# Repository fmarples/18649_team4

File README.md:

# Team 4 Lab 2

**Managed session:** `start.py` starts/connects the Pi bridge and wheel GUI;
`stop.py` stops only the managed pair. Start can cause motion; keep hands clear
and pedals released. See [session ownership and logs](doc/ONE_CLICK_START.md).

`main` contains the combined Part 3 actuator implementation and Part 4 Zephyr
scheduling. Use the current firmware for combined motor, brake, steering and
blinker testing; there is no separate Part 4 application or required rollback.
Part 3.5 ADC acquisition is implemented with nominal ACS712 5A calibration and
upper-ADC-rail clipping at -4320 mA for reversed motor sensors and +4320 mA for
servo. There is no symmetric current cap. Physical calibration and combined timing remain pending.

## Code

- `stm32_zephyr/`: NUCLEO-F401RE firmware, UART parsing, motor/PID control,
  steering, blinkers, self-test, scheduling, current interface and timing markers.
- `pi/`: UDP-to-UART bridge, CRC protocol and optional GPIO timing markers.
- `windows/`: wheel-proxy launcher with event-filtered physical-input logs and
  read-only current charts, servo console and firmware build helper.
- `bringup/encoder_test/` and `bringup/motor_test/`: independent diagnostics.
- `tests/` and `test_protocol.py`: software and explicitly invoked hardware tests.
- `tools/`: generated-build checks, bounded QEMU runner and status-log summary.

The Part 3 integration commit is `3b04a43`; the Part 4 implementation commit is
`18da014`. The retired branches are preserved as archive tags.

## Architecture and operating policy

`Logitech wheel -> Windows proxy -> UDP 8000 -> Pi -> USART1 -> STM32 actuators`

The Pi link uses 115200 baud, 8N1. Commands carry raw wheel/pedal values and
buttons; status carries system state and current validity. Deploy matching
Pi and STM32 versions and all `pi/*.py` dependencies together. Read-only status
returns to the laptop on UDP 8002, separate from force-feedback UDP 8001.

One priority-1 owner applies motor outputs before steering and lamps. Status,
current sampling and USB diagnostics run at priorities 2, 3 and 4 respectively.
The three current channels use ADC1 with nominal calibration; failed or stale
acquisition is unavailable. Current telemetry does not control actuators.

Steering embeds the tracked 1200/1600/2000 us calibration. Boot and fault/link
recovery wait for healthy Pi commands and a centered wheel before LIVE. Vehicle
steering does not require a USB heartbeat; manual calibration retains its lease.
The servo console's OFF command does not stop motors. See the
[integration design](doc/INTEGRATION.md) and [protocol](PROTOCOL.md) for details.

## Team documentation

- [September 28 bench summary: changes, tests and remaining work](doc/SESSION_2026-09-28.md)
- [Actuator stability investigation and verification](doc/ACTUATOR_STABILITY.md)
- [Task table and scheduling rationale](PART4_TASK_TABLE.md)
- [Hardware BOM/power record](doc/HARDWARE.md) and [pin assignments](doc/LAB3_PINOUT.md)
- [Encoder calibration](doc/ENCODER_SPEC.md) and [motor characterization](doc/MOTOR_CHARACTERIZATION.md)
- [Current-sensor backend contract](doc/CURRENT_SENSOR_HANDOFF.md)
- [GUI telemetry and physical input logging](doc/GUI_TELEMETRY.md)
- [ADC hang diagnosis and grounding verification](doc/CURRENT_ADC_DIAGNOSIS.md)
- [Centered-start steering policy and evidence](doc/STEERING_AUTONOMOUS.md)
- [Timing points and measurement method](doc/PART4_TIMING.md)
- [Blank measurement worksheet](doc/PART4_MEASUREMENTS.csv)
- [Software verification record](doc/PART4_SOFTWARE_RESULTS.md)
- [Steering evidence](doc/PART3_3_RESULTS.md) and [blinker evidence](doc/PART3_4_RESULTS.md)
- [Lab 2 handout](doc/18-449_649%20Lab2%20-%20Sensors%20and%20Actuators%20v1_0.pdf)

The integrated image builds and software verification is recorded in the linked
reports, including host-dependent test skips. Combined motor/steering operation
and three-channel current acquisition have been observed on the stability branch.
Transient link timeouts, current calibration and physical timing remain open;
software test results do not certify those measurements.

## Build and software checks

From the repository root on Windows, with an installed Zephyr workspace/SDK:

```powershell
.\windows\build_part4.ps1 -ZephyrWorkspace 'C:\path\to\zephyrproject' -Sdk 'C:\path\to\zephyr-sdk'
```

This only builds and checks configuration; it does not flash or open hardware.
Output: `build/part4/zephyr/zephyr.bin`. Generic software checks in the appropriate
Python environment are:

```sh
python -m unittest discover -s tests -p "test_*.py" -v
python test_protocol.py -v
```

Native C wrappers may skip without host GCC; the ARM/QEMU suite lives in
`tests/integration/`. Build outputs and run logs are ignored by Git.
Personal operator walkthroughs and tutoring notes are maintained outside this
repository.

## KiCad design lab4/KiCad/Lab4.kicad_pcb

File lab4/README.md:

# Lab 4: three-zone controller PCB

The PCB is named **649 Team 4**. The [November 2 Anson review revision](November2-Anson-review.md)
redraws the schematic, identifies F1's existing 10 A candidate, moves the
motor clamps/left connector and three bypass capacitors, and improves two
local CAN pairs. Support holes, stack, part identities and BOM quantities
are unchanged. Use the current matching review package.

The [schematic formatting update](Schematic-format-review.md) adds blue dashed
function boxes, stacked CAN sections and consistent headings to match the
staff example. All connections and the PCB are unchanged from `7644128`.

Original `6945466` was submitted to Gradescope on October 30; its archives
reached staff. The team linked `4895895` to Anson on November 2. The new
November 2 files are prepared but have not been sent. Staff acceptance and
powered validation are not claimed.

We are designing a four-layer KiCad PCB with two STM32F401RET6 chips, six
MCP2515/CAN-transceiver interfaces, motor and servo current sensing, and a
3S LiPo supply using the CNHL S220403BK / Hitec 44295 pair approved by Anson on October 28. The Raspberry Pi remains a separate board connected through
its 40-pin header.

The [October 29 course updates](Course-updates-October29.md) close the question
of whether extra L298 hardware protection is mandatory (it is optional) and
confirm that rigid mounting, rather than a prescribed hole set, is required.
The optional camera is not included in the current power allocation. The saved
copper stack is unchanged; 2 oz would require a revised manufacturing review.

We selected the required scope only: keep the course L298 and omit extra
hardware current limiting and the camera. The [input-fuse review](Fuse-and-scope-review.md)
and [Pi conductor mesh](Pi-feed-review.md) are complete for their stated
assumptions. The 3 A mesh is retained as a deferred stress case; the current
load-specific result and limitations are in [Prototype-operating-review.md](Prototype-operating-review.md). No optional-circuit decision or new hole measurement
is holding up the review. The [Lab 1 revision history](https://docs.google.com/document/d/182TcM6g2DfyiQt0xGXAkl2lv_5BjBLEOPw9v7Lpieis)
now records the October 29 hardware configuration.

## October 28 capacitor and chassis allowance revision

The latest [power-route/package correction](Power-route-revision.md) widens
779 power segments and fixes C802 to the manufacturer's D10/P5 footprint.
All native checks and 331 targeted connections pass; the October 29
[package audit](Critical-package-review.md) now covers 282 components.
The L298 uses a local footprint with 1.1 mm finished plated holes for better
lead-clearance tolerance; pin centers, copper pads and heatsink anchors are unchanged.
These checks cover the listed package geometry and critical pin nets, not
complete operating qualification. The [review export](review-package/REVIEW-ONLY.txt)
contains matching schematic/layer PDFs, 3D views, Gerbers/drills and BOM/CPL
files. It is ready for the course
prototype fabrication review, with no order or TA acceptance claimed.
[Prototype-operating-review.md](Prototype-operating-review.md) separates the
completed planning review from required assembly/bring-up checks and optional stress work.

We selected rear chassis pair A1/A2 after the team confirmed both holes are
unused and accessible. CAD dimensions are 47.870 mm front, 73.01493 mm rear
and 233.21155 mm between rows; team measurements are about 48, 73.45 and
232.85 mm respectively. The PCB is now 120 × 247.21155 mm, extended
13.21155 mm rearward. H1–H4 use 4.0 mm NPTH holes for M3 with 4 mm edge
exclusions; Pi supports remain 2.7 mm with 3 mm exclusions. The earlier
cardboard test used the previous pattern. See
[Mounting-tolerance-revision.md](Mounting-tolerance-revision.md).

We replaced the six small buck-output capacitors and added ten parallel
capacitors. Each input bank is now 66 µF nominal; servo/Pi/logic output banks
are 88/66/66 µF. The selected 1210 parts and 68/91/30 pF feed-forward values
are documented in [Capacitor-bank-review.md](Capacitor-bank-review.md).
The bias/tolerance/temperature/aging screen passes the stated capacitance
targets. This is a calculated design screen, not measured transient or
thermal qualification.

## October 27 mounting and encoder revision

We implemented the 3 mm clearance from the **finished hole edge** at all
four chassis and four Pi support holes. The exclusions cover components,
tracks, vias and filled copper on all four layers. The Pi socket is now
**Samtec ESQ-118-44-L-D**, mating physical Pi pins **3–38**. The first socket
pair must align with Pi pins 3/4, not 1/2. Pin 4 alone supplies 5 V. All used
signals and Lab 3 assignments are unchanged. Do not substitute the old
40-contact socket: it violates the hole-edge clearance.

We also installed the 6396BG anchor footprint, moved U80/C800/C802/J80,
and repaired local routing. A new 4.0 V encoder rail replaces the marginal
3.3 V encoder feed; the signal buffer and its pull-ups remain at 3.3 V.
See [Mounting-and-encoder-revision.md](Mounting-and-encoder-revision.md)
for exact parts, calculations, checks and remaining limitations.

The current board has 300 electrical footprints plus eight supports and
HS80, 20,296 track/via items and six filled ground zones. The targeted routing
check covers 331 connections. Fresh native findings and source hashes are in
[Fabrication-check.json](Fabrication-check.json). These checks do not authorize
an order. The current planning review is complete; team/TA review precedes
fabrication, and harness/fuse selection, cutoff integration and controlled
powered validation precede LiPo use. The capacitor
selection and routing revision is implemented; loop/transient and thermal
behavior still require qualified review and later prototype validation.

The reference [layer stack](Layer-stack.md) and initial
[return-path review](Return-path-review.md) document the copper assumptions and remaining checks.
The [supply-path screening](Supply-path-review.md) includes shared-load allocation;
remaining voltage and thermal findings are listed in the power-margin review.
The [CAN geometry audit](CAN-geometry-review.md) records branch lengths and
the repaired sampled ground reference. The [solder-via review](Solder-via-review.md)
records the completed overlap correction and remaining mask/assembly checks.
On October 26 staff explicitly allowed four-layer boards. The saved PCB now
uses F.Cu / In1.Cu ground / In2.Cu signals / B.Cu, with inner-layer keep-outs. Teams
should plan stencil assembly, not assume board-house assembly. See the dated
course updates in Fabrication-review.md.
The last checked two-layer layout is preserved at the
[lab4-two-layer-archive tag](https://github.com/fmarples/18649_team4/tree/lab4-two-layer-archive/lab4)
(commit `59be0b1`). It is a historical, partially routed checkpoint; use the
current `lab4` branch for further design work.

The selected [LiPo battery and charger](Battery-LiPo.md) replace the historical
NiMH candidates. Anson approved the exact Amazon pair; all other new parts
must use DigiKey/Mouser or confirmed course stock. The existing Drive purchasing
workbook matches the current active CSV. A selection/approval is not
an order or a completed hardware test.

The October 24 team reply relays Anson's acceptance of the 6396BG heatsink
and deferral of motor stall/L298 loss/temperature measurements for that
preliminary review. Its drawing-based mounting arrangement is now implemented;
thermal performance and motor-fault protection are still unvalidated. The
TAs confirmed on October 23 that teams will assemble all SMD parts themselves,
with TechSpark oven access tentative. BOM-Hand-assembly.csv is the active
assembly list; use course v3 stock first. This is not a fabrication or
purchasing release. The October 24 review covered schematic, BOM and high-level
design; the board layout deadline is October 29.

## Shared report and files

- [Fabrication review](Fabrication-review.md): current revision, review limits and
  fresh-check instructions. The original Gradescope submission is complete;
  staff acceptance and the corrected-file handoff are separate actions.
- [Must-do list](https://docs.google.com/document/d/1k5grd6PXWf11GlPkxlc1w4cDT9LOGJRj_YvyB7UWkLg/edit): remaining team actions, deferred work and completed items.
- [Lab 4 Writeup](https://docs.google.com/document/d/1zMR_S5QoFPES1BhswG5bhpLGAib2P71ri6rK2hKzBcc/edit): edit this same report for future revisions.
- [Team Lab 4 Drive folder](https://drive.google.com/drive/u/1/folders/1j7L880-h1lnl-udWRu19jh2Ww-18leLq).
- [Editable system diagram](Lab4-System.drawio), with [SVG](Lab4-System.svg) and [PNG](Lab4-System.png) previews.

The shared Google Doc is the report. This repository holds the editable design
sources, technical calculations and verification records.

Lab 4 disables Git line-ending conversion locally through `.gitattributes`.
The engineering reports and review manifest hash exact file bytes; preserving
them makes the checked CAD/export files consistent across checkouts and Git
archives. A text-only line-ending change still requires refreshing its hashes.

Use this `lab4/` directory on the `lab4` branch as the source of truth for
KiCad files, local libraries, the editable diagram, BOMs and engineering tables.
Drive holds the shared report, original course references and raw measurement
evidence. There is no automatic synchronization between GitHub and Drive;
link to these design files from Drive instead of uploading editable copies.

When the design changes, regenerate the affected schematic PDF, BOM and checks
from the same source revision and commit them together. Record the commit used
for a TA submission so the reviewed version can be recovered later.

## Design files

| File | Contents |
| --- | --- |
| [KiCad/Lab4.kicad_pro](KiCad/Lab4.kicad_pro) | Open this project in KiCad 10. |
| [KiCad/Lab4.kicad_sch](KiCad/Lab4.kicad_sch) | Overview linking the Front, Rear, Cockpit and Power sheets. |
| [KiCad/Lab4.kicad_pcb](KiCad/Lab4.kicad_pcb) | Editable 120 × 247.21155 mm PCB with all required connections routed; electrical release review remains open. |
| [Placement-overview.png](Placement-overview.png) | Direct Pi stack: bottom socket and top circuitry above the Pi. |
| [Pi-stack-side-view.png](Pi-stack-side-view.png) | Proposed 22 mm Pi gap and 35 mm chassis spacers; physical fit pending. |
| [Placement-detail.svg](Placement-detail.svg) | Native KiCad component outlines and references. |
| [Placement-fit-template.pdf](Placement-fit-template.pdf) | Two-page true-size PCB/Pi fit aid, side view and measurement fields; not a drill template. |
| [Placement-review.md](Placement-review.md) | Placement decisions, verification results and remaining work. |
| [Placement-check.json](Placement-check.json) | Netlist, outline, Pi-space and mounting-margin checks. |
| [KiCad/Placement-DRC.json](KiCad/Placement-DRC.json) | Fresh native DRC and schematic parity: zero findings and zero missing connections. |
| [Lab4-Circuits.pdf](Lab4-Circuits.pdf) | Five-page schematic preview. |
| [Pin-map.csv](Pin-map.csv) | Per-zone signal names, physical pins, modes and unresolved integration notes. |
| [Power-design.html](Power-design.html) | Proposed power tree, component calculations and validation limits. |
| [Power-budget.csv](Power-budget.csv) | Four rail allocations; average loads remain unmeasured. |
| [Current-evidence.md](Current-evidence.md) | Why existing Lab 2 logs cannot establish calibrated average current. |
| [Current-measurements.csv](Current-measurements.csv) | Rail/condition record for the remaining measurements. |
| [Parts-review.md](Parts-review.md) | Course v3 reconciliation, documented selections and physical checks. |
| [Course-stock-v3.csv](Course-stock-v3.csv) | Exact named course-stock parts and source links. |
| [Review-package.md](Review-package.md) | October 24 deliverables and remaining review decisions. |
| [Power-calculations.json](Power-calculations.json) | Calculated regulator ripple, peak current and enable thresholds. |
| [Preliminary-BOM.csv](Preliminary-BOM.csv) | Placed quantities and additional planned parts, with procurement status. |
| [KiCad/Circuit-BOM.csv](KiCad/Circuit-BOM.csv) | The 300 components currently placed in the schematic. |
| [BOM-Hand-assembly.csv](BOM-Hand-assembly.csv) | Active course/team-assembly procurement view. |
| [BOM-JLC-hybrid.csv](BOM-JLC-hybrid.csv) | Historical catalog comparison; not the selected course assembly plan. |
| [Assembly-options.md](Assembly-options.md) | Process differences, equipment and sourcing checks. |
| [Actuator-design.md](Actuator-design.md) | Motor, encoder, servo and lamp circuits; ratings and connector pin definitions. |
| [Design-review.csv](Design-review.csv) | Earlier preliminary-review snapshot; its battery, mounting and routing status is superseded by the current shared must-do list and dated reviews above. |
| [Interface-review.csv](Interface-review.csv) | Interface allocation notes and actual host-pin/net connections. |
| [Measurements-to-record.csv](Measurements-to-record.csv) | Confirmed mounting geometry and remaining physical/electrical measurements. |
| [Verification.txt](Verification.txt) | Checks performed and their limits. |
| [KiCad/ERC.txt](KiCad/ERC.txt) | Current schematic: zero errors/warnings; engineering limitations remain. |
| [check_netlist.py](check_netlist.py) | Repeatable connectivity/BOM checks on a KiCad XML export. |
| [circuit-pin-connections.json](circuit-pin-connections.json) | Placed component pin/net metadata for comparison with the schematic. |

Keep the local `Lab4_Power.kicad_sym`, `Lab4_Logic.kicad_sym`, `Lab4_Power.pretty`,
`Lab4_Mechanical.pretty`, `Lab4_Mechanical.3dshapes`, `sym-lib-table` and
`fp-lib-table` beside the KiCad project. Their paths use `${KIPRJMOD}` and travel
with the repository. The other footprints come from the standard KiCad library.

## Power and pin decisions

We selected the TA-approved CNHL S220403BK 3S LiPo and Hitec 44295 charger.
Amazon is permitted for both. All active new non-battery/charger purchases
use DigiKey/Mouser or explicitly requested course stock. The pack body fits
the measured battery envelope with the supplier's dimensional allowance;
actual retention and wiring are assembly checks. Old NiMH entries have zero
purchase quantity. See [Battery-LiPo.md](Battery-LiPo.md) for ratings, wiring,
charging and the implemented divider/standalone cutoff guard. MCU integration,
power-filter qualification and motor/fuse protection are not complete.
The proposed branches are the unregulated motor supply, 6.6 V servo buck,
5.1 V Pi/devices buck and 3.318 V logic buck. The protected-input electrical
target is 8–15 V; this does not define the cells' allowed discharge voltage.

The pin proposal uses the Lab 3 candidate/WCET overlays at commit `c4fba58` as
its baseline. Lab 3 CAN, timing and LED assignments are retained or reserved.
PB11 is unavailable in the STM32F401RE's LQFP64 package, so PC9 is proposed for
that PID marker; PC8 remains the WCET task probe. New actuator and ADC signals
avoid those timing pins. This branch does not implement or flash the PCB
firmware changes. Pin-map.csv is a signal allocation, not a complete MCU
power/decoupling pinout.

Both bare-MCU support circuits are now placed: VDD bypass capacitors, filtered
VDDA, reset and BOOT0 circuits, separate reset/self-test buttons, SWD and UART
headers. Each MCU's VCAP1 pin has its own **4.7 µF** capacitor to ground, as
specified for LQFP64 in the [STM32F401RE datasheet](https://www.st.com/resource/en/datasheet/stm32f401re.pdf).
VCAP1 is an internal-regulator output, not a GPIO or a 3.3 V supply input.
The initial clock plan uses internal HSI/PLL; the Nucleo ST-LINK clock is absent.

We added the Pi socket, twelve diagnostic LEDs with individual 1 kΩ
resistors, and probe rows matching the Lab 3 handout. Extra probes have separate
headers. The Pi's 3.3 V output remains disconnected from the PCB's independent
3.3 V regulator. Do not connect separate USB-C power while the board supplies
the Pi through pin 4; power-path isolation is not implemented.

J70 is a bottom-mounted Samtec ESQ-118-44-L-D socket covering Pi pins 3–38, aligned
directly to a component-side-up Pi below the main PCB. No GPIO cable is planned.
Top-side cockpit CAN circuitry occupies part of that same area. We propose
22 mm Pi spacers and 35 mm chassis spacers, now supported by the October 24
Pi caliper measurements and nominal clearance calculations in
[Mechanical-evidence.md](Mechanical-evidence.md). Actual assembly is untested. See the
placement review for contact insertion, underside-tail limits, cooling/Wi-Fi
checks. The implemented 3 mm Pi hole-edge exclusions pass the saved-board audit.

The root sheet explicitly joins the power, ground and two CAN backbones.
SPI, clocks, reset and actuator signals remain within their owning zones.
The local MCP2515 symbol marks SO as tri-state, matching
[Microchip DS20001801K, Figure 12-11](https://www.microchip.com/content/dam/mchp/documents/APID/ProductDocuments/DataSheets/MCP2515-Family-Data-Sheet-DS20001801K.pdf).
The general ERC output-conflict check stays enabled. The local Pi symbol treats
the board-fed 5 V/GND connector pins as inputs and its hidden stacked pins as
passive; this avoids an implicit global 5 V connection. Power flags identify
the battery, regulator outputs and supplies after passive filters; they do not
prove voltage regulation or available current.

The proposed Pi mapping is A=CE0/IRQ25 and B=CE1/IRQ24. Confirm the installed
device-tree configuration and physical bus labels before relying on Linux
`can0`/`can1` enumeration.

## Remaining work by stage

- Before fabrication: hand off the corrected matching files, record staff's
  review and finish any remaining feedback before **Monday night, November 2**.
  The original Gradescope submission is complete. See the
  [November 1 announcement](https://18449-f26.slack.com/archives/C0BRYGTD4HH/p1793568222872769).
  No new hole measurements or sustained 3 A Pi qualification are requested.
- Before ordering/assembly: reconcile actual stock, settle the servo lead and
  solder process. Current purchasing exceptions remain visible in the BOM.
- Before LiPo operation: staged bench commissioning, fuse/harness selection,
  battery-guard application integration and physical/electrical acceptance.
  These remain required; see [the operating review](Prototype-operating-review.md).
- Optional/deferred: sustained 3 A Pi tests, extra peripherals/current limiter,
  deliberate stall tests, a 2 oz redesign and expanded simulation.

## Rechecking with KiCad

From this directory, with `kicad-cli` from KiCad 10 on PATH:

```sh
kicad-cli sch export pdf -o Lab4-Circuits.pdf KiCad/Lab4.kicad_sch
kicad-cli sch erc -o KiCad/ERC.txt KiCad/Lab4.kicad_sch
kicad-cli sch export netlist --format kicadxml -o lab4-check.xml KiCad/Lab4.kicad_sch
python check_netlist.py lab4-check.xml
```

PDF export checks that KiCad can parse the project. ERC checks electrical
connectivity; neither proves component ratings, footprint dimensions, thermal
performance or fabrication readiness. Record any changed findings rather than
assuming that successfully exporting the PDF means the board is complete.
The XML is a temporary check artifact; it need not be committed.

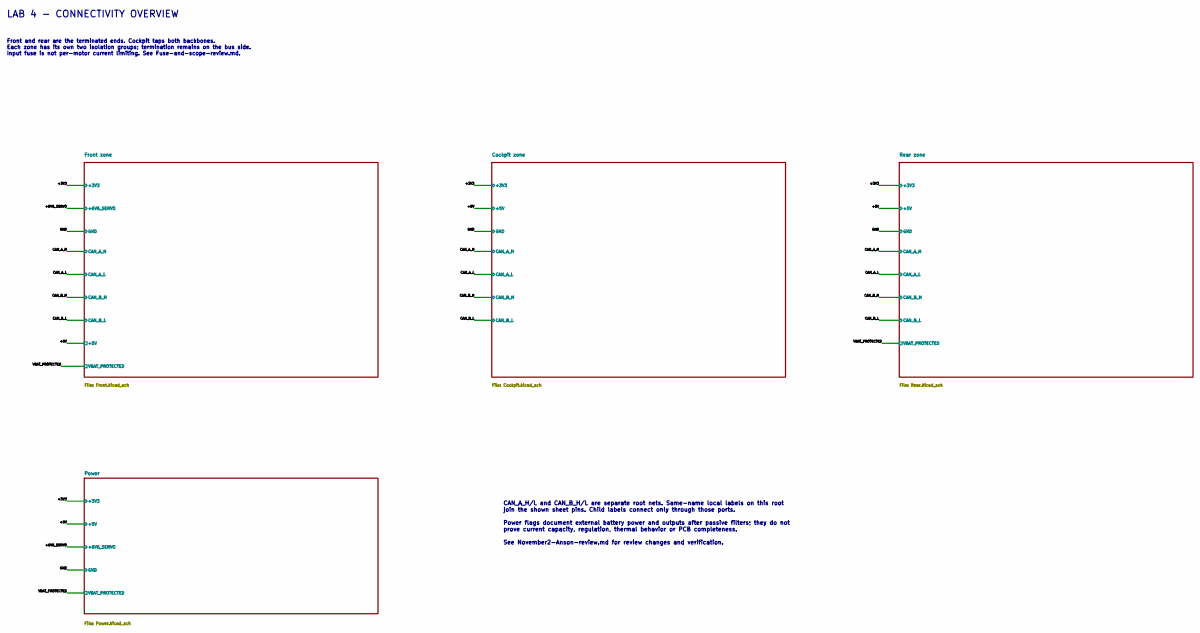
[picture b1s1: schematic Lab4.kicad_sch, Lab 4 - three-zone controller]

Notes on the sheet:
LAB 4 - CONNECTIVITY OVERVIEW
Front and rear are the terminated ends. Cockpit taps both backbones. Each zone has its own two isolation groups; termination remains on the bus side. Input fuse is not per-motor current limiting. See Fuse-and-scope-review.md.
CAN_A_H/L and CAN_B_H/L are separate root nets. Same-name local labels on this root join the shown sheet pins. Child labels connect only through those ports. Power flags document external battery power and outputs after passive filters; they do not prove current capacity, regulation, thermal behavi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

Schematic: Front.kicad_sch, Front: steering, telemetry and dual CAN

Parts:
C1, C2, C102, C103, C104, C142, C143, C144, C580: 100n; C_0603_1608Metric; MPN KGM15AR71C104KT
C100, C101, C140, C141: 18p C0G 50V; C_0603_1608Metric; MPN GRM1885C1H180JA01D
C500: 100n VDD19; C_0603_1608Metric; MPN KGM15AR71C104KT
C501: 100n VDD32; C_0603_1608Metric; MPN KGM15AR71C104KT
C502: 100n VDD48; C_0603_1608Metric; MPN KGM15AR71C104KT
C503: 100n VDD64; C_0603_1608Metric; MPN KGM15AR71C104KT
C504: 100n VBAT; C_0603_1608Metric; MPN KGM15AR71C104KT
C505: 4.7u VDD bulk; C_0805_2012Metric; MPN GRM21BR71C475KE51L
C506: 4.7u VCAP1; C_0805_2012Metric; MPN GRM21BR71C475KE51L
C507: 100n VDDA; C_0603_1608Metric; MPN KGM15AR71C104KT
C508: 1u VDDA; C_0603_1608Metric; MPN CC0603JRX7R7BB105
C509: 100n NRST; C_0603_1608Metric; MPN KGM15AR71C104KT
C510: 100n TEST; C_0603_1608Metric; MPN KGM15AR71C104KT
D510: STATUS green; LED_0603_1608Metric; MPN LTST-C190GKT
D511: ERR red; LED_0603_1608Metric; MPN LTST-C190KRKT
D512: DEG_A yellow; LED_0603_1608Metric; MPN LTST-C190KSKT
D513: DEG_B yellow; LED_0603_1608Metric; MPN LTST-C190KSKT
FB50: 600R @100MHz; L_0603_1608Metric; MPN 742863160
J1: Sense test points; PinHeader_1x03_P2.54mm_Vertical
J10: CAN A isolation; PinHeader_2x02_P2.54mm_Vertical
J11: CAN A test; PinHeader_1x04_P2.54mm_Vertical
J14: CAN B isolation; PinHeader_2x02_P2.54mm_Vertical
J15: CAN B test; PinHeader_1x04_P2.54mm_Vertical
J90: Servo: GND / 6.6V / PWM; Hirose_DF63M-3P-3.96DSA_1x03_P3.96mm_Vertical; MPN DF63M-3P-3.96DSA
J500: BOOT recovery; PinHeader_1x02_P2.54mm_Vertical; MPN 2.54 mm breakaway header
J501: SWD (2.54mm); PinHeader_1x06_P2.54mm_Vertical; MPN 2.54 mm breakaway header
J502: 3.3V TTL UART; PinHeader_1x03_P2.54mm_Vertical; MPN 2.54 mm breakaway header
J503: LAB3 rows 1-13; PinHeader_1x13_P2.54mm_Vertical; MPN 2.54 mm breakaway header
J504: Additional probes; PinHeader_1x08_P2.54mm_Vertical; MPN 2.54 mm breakaway header
J505: Reserved / encoder probes; PinHeader_1x04_P2.54mm_Vertical; MPN 2.54 mm breakaway header
J550: FRONT LEFT lamp; PinHeader_1x02_P2.54mm_Vertical; MPN 2.54 mm breakaway header
J551: FRONT RIGHT lamp; PinHeader_1x02_P2.54mm_Vertical; MPN 2.54 mm breakaway header
JP10: TERM A; PinHeader_1x02_P2.54mm_Vertical
JP14: TERM B; PinHeader_1x02_P2.54mm_Vertical
Q550, Q551: MMBT3904; SOT-23; MPN MMBT3904-7-F
R1: 10mR / 1W / 1%; Vishay_WSL2512_7m_to_500m; MPN WSL2512R0100FEA
R2: 4.7k; R_0603_1608Metric; MPN RC0603FR-074K7L
R100, R101, R140, R141: 10k; R_0603_1608Metric; MPN CRCW060310K0FKEA
R102, R142: 120R; R_0603_1608Metric; MPN RC0603FR-07120RL
R500: 10k BOOT0; R_0603_1608Metric; MPN CRCW060310K0FKEA
R501: 10k NRST; R_0603_1608Metric; MPN CRCW060310K0FKEA
R502: 10k TEST pullup; R_0603_1608Metric; MPN CRCW060310K0FKEA
R510, R511, R512, R513: 1k; R_0603_1608Metric; MPN ERJ-3EKF1001V
R530: 10k PWM pulldown; R_0603_1608Metric; MPN CRCW060310K0FKEA
R540: 100R; R_0603_1608Metric; MPN CRCW0603100RFKEA
R550, R551: 2.2k; R_0603_1608Metric; MPN CRCW06032K20FKEA
R560, R561: 100k; R_0603_1608Metric; MPN CRCW0603100KFKEA
R570, R571: 220R; R_0603_1608Metric; MPN CRCW0603220RFKEA
R580: 100k 0.1%; R_0603_1608Metric; MPN RT0603BRD07100KL
R581: 10k 0.1%; R_0603_1608Metric; MPN RT0603BRD0710KL
SW50, SW51: SWT0210-045026GSA; GCT_SWT0210_4.5x4.5mm; MPN SWT0210-045026GSA
U1: INA180A2IDBVR; SOT-23-5; MPN INA180A2IDBVR
U10, U14: MCP2515T-I/ST; TSSOP-20_4.4x6.5mm_P0.65mm; MPN MCP2515T-I/ST
U11, U15: SN65HVD231DR; SOIC-8_3.9x4.9mm_P1.27mm; MPN SN65HVD231DR
U50: STM32F401RET6TR; LQFP-64_10x10mm_P0.5mm; MPN STM32F401RET6TR
Y10, Y14: 16 MHz; Crystal_SMD_3225-4Pin_3.2x2.5mm; MPN CX3225SB16000H0FLJCC

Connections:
/+3V3: C1.1, C103.1, C104.1, C143.1, C144.1, C500.1, C501.1, C502.1, C503.1, C504.1, C505.1, FB50.1, J500.1, J501.1, R100.1, R101.1, R140.1, R141.1, R501.1, R502.1, U1.5 (V+), U10.4 (~TX0RTS), U10.5 (~TX1RTS), U10.7 (~TX2RTS), U10.20 (VDD), U11.3 (VCC), U14.4 (~TX0RTS), U14.5 (~TX1RTS), U14.7 (~TX2RTS), U14.20 (VDD), U15.3 (VCC), U50.1 (VBAT), U50.19 (VDD), U50.32 (VDD), U50.48 (VDD), U50.64 (VDD); also elsewhere on the board
/+5V: R570.1, R571.1; also elsewhere on the board
/+6V6_SERVO: R1.1, U1.3 (+); also elsewhere on the board
/CAN_A_H: J10.2, J11.3, JP10.1 (A); also elsewhere on the board
/CAN_A_L: J10.4, J11.4, R102.2; also elsewhere on the board
/CAN_B_H: J14.2, J15.3, JP14.1 (A); also elsewhere on the board
/CAN_B_L: J14.4, J15.4, R142.2; also elsewhere on the board
/Front zone/BATTERY_ADC: C580.1, R580.2, R581.1, U50.17 (PA3)
/Front zone/F_A_H_LOCAL: J10.1, U11.7 (CANH)
/Front zone/F_A_L_LOCAL: J10.3, U11.6 (CANL)
/Front zone/F_A_OSC1: C100.1, U10.9 (OSC1), Y10.1
/Front zone/F_A_OSC2: C101.1, U10.8 (OSC2), Y10.3
/Front zone/F_A_RESET: C102.1, R100.2, U10.19 (~RESET)
/Front zone/F_A_RXD: J11.2, U10.2 (RXCAN), U11.4 (R)
/Front zone/F_A_TERM: JP10.2 (B), R102.1
/Front zone/F_A_TXD: J11.1, U10.1 (TXCAN), U11.1 (D)
/Front zone/F_BOOT0: J500.2, R500.1, U50.60 (BOOT0)
/Front zone/F_B_H_LOCAL: J14.1, U15.7 (CANH)
/Front zone/F_B_L_LOCAL: J14.3, U15.6 (CANL)
/Front zone/F_B_OSC1: C140.1, U14.9 (OSC1), Y14.1
/Front zone/F_B_OSC2: C141.1, U14.8 (OSC2), Y14.3
/Front zone/F_B_RESET: C142.1, R140.2, U14.19 (~RESET)
/Front zone/F_B_RXD: J15.2, U14.2 (RXCAN), U15.4 (R)
/Front zone/F_B_TERM: JP14.2 (B), R142.1
/Front zone/F_B_TXD: J15.1, U14.1 (TXCAN), U15.1 (D)
/Front zone/F_CS_A: R101.2, U10.18 (~CS), U50.58 (PB6)
/Front zone/F_CS_B: R141.2, U14.18 (~CS), U50.38 (PC7)
/Front zone/F_DEG_A_LED: J503.7, R512.1, U50.26 (PB0)
/Front zone/F_DEG_A_LED_ANODE: D512.2 (A), R512.2
/Front zone/F_DEG_B_LED: J503.8, R513.1, U50.27 (PB1)
/Front zone/F_DEG_B_LED_ANODE: D513.2 (A), R513.2
/Front zone/F_DIR_A_MARKER: J505.4, U50.29 (PB10)
/Front zone/F_ERROR_LED: J503.13, J504.4, R511.1, U50.8 (PC0)
/Front zone/F_ERROR_LED_ANODE: D511.2 (A), R511.2
/Front zone/F_FRONT_LEFT_LED: J503.10, R550.1, U50.20 (PA4)
/Front zone/F_FRONT_LEFT_LED_BASE: Q550.1 (B), R550.2, R560.1
/Front zone/F_FRONT_LEFT_LED_PLUS: J550.1, R570.2
/Front zone/F_FRONT_LEFT_LED_SINK: J550.2, Q550.3 (C)
/Front zone/F_FRONT_RIGHT_LED: J503.11, R551.1, U50.61 (PB8)
/Front zone/F_FRONT_RIGHT_LED_BASE: Q551.1 (B), R551.2, R561.1
/Front zone/F_FRONT_RIGHT_LED_PLUS: J551.1, R571.2
/Front zone/F_FRONT_RIGHT_LED_SINK: J551.2, Q551.3 (C)
/Front zone/F_INT_A: U10.13 (~INT), U50.43 (PA10)
/Front zone/F_INT_B: U14.13 (~INT), U50.57 (PB5)
/Front zone/F_MISO: U10.17 (SO), U14.17 (SO), U50.22 (PA6)
/Front zone/F_MOSI: U10.16 (SI), U14.16 (SI), U50.23 (PA7)
/Front zone/F_PID_MARKER: J504.7, U50.40 (PC9)
/Front zone/F_PWM_SET_MARKER: J505.3, U50.62 (PB9)
/Front zone/F_RELAY_TX_MARKER: J503.12, U50.37 (PC6)
/Front zone/F_RESET_N: C509.1, J501.5, R501.2, SW50.1, U50.7 (NRST)
/Front zone/F_RX_A_MARKER: J503.3, U50.10 (PC2)
/Front zone/F_RX_B_MARKER: J503.4, U50.11 (PC3)
/Front zone/F_SCK: U10.14 (SCK), U14.14 (SCK), U50.21 (PA5)
/Front zone/F_SELFTEST_BUTTON: C510.1, J504.3, R502.2, SW51.1, U50.2 (PC13)
/Front zone/F_SERVO_PWM: J503.9, R530.1, R540.1, U50.42 (PA9)
/Front zone/F_STATUS_LED: R510.1, U50.50 (PA15)
/Front zone/F_STATUS_LED_ANODE: D510.2 (A), R510.2
/Front zone/F_STEER_TASK_MARKER: J504.6, U50.9 (PC1)
/Front zone/F_SWCLK: J501.2, U50.49 (PA14)
/Front zone/F_SWDIO: J501.4, U50.46 (PA13)
/Front zone/F_TASK_PROBE: J504.5, U50.39 (PC8)
/Front zone/F_TX_A_MARKER: J503.5, U50.14 (PA0)
/Front zone/F_TX_B_MARKER: J503.6, U50.15 (PA1)
/Front zone/F_UART_CONSOLE_RX: J502.2, U50.45 (PA12)
/Front zone/F_UART_CONSOLE_TX: J502.1, U50.44 (PA11)
/Front zone/F_VCAP1: C506.1, U50.30 (VCAP1)
/Front zone/F_VDDA: C507.1, C508.1, FB50.2, U50.13 (VREF+)
/Front zone/SERVO_ADC: C2.1, J1.2, J504.8, R2.2, U50.16 (PA2)
/Front zone/SERVO_PWM_OUT: J90.3, R540.2
/Front zone/SERVO_RAW: J1.1, R2.1, U1.1
/Front zone/SERVO_VPLUS: J90.2, R1.2, U1.4 (-)
/GND: C1.2, C2.2, C100.2, C101.2, C102.2, C103.2, C104.2, C140.2, C141.2, C142.2, C143.2, C144.2, C500.2, C501.2, C502.2, C503.2, C504.2, C505.2, C506.2, C507.2, C508.2, C509.2, C510.2, C580.2, D510.1 (K), D511.1 (K), D512.1 (K), D513.1 (K), J1.3, J90.1, J501.3, J501.6, J502.3, J503.1, J503.2, J504.1, J504.2, J505.1, J505.2, Q550.2 (E), Q551.2 (E), R500.2, R530.2, R560.2, R561.2, R581.2, SW50.2, SW51.2, U1.2 (GND), U10.10 (VSS), U11.2 (GND), U11.8 (Rs), U14.10 (VSS), U15.2 (GND), U15.8 (Rs), U50.12 (VSSA), U50.18 (VSS), U50.31 (VSS), U50.47 (VSS), U50.63 (VSS), Y10.2 (G), Y10.4 (G), Y14.2 (G), Y14.4 (G); also elsewhere on the board
/VBAT_PROTECTED: R580.1; also elsewhere on the board

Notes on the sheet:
CAN A: controller, transceiver and isolation
16 MHz; SPI from zone processor
CAN B: controller, transceiver and isolation
STM32F401: processor, supplies and recovery
100 nF at each VDD pin; VCAP is a dedicated regulator output.
Servo supply, high-side current sense and PWM
Vehicle lamps
Battery voltage monitor
Accessible test headers
Lab 3 pin assignments retained. Do not apply 5 V to MCU/ADC inputs.
